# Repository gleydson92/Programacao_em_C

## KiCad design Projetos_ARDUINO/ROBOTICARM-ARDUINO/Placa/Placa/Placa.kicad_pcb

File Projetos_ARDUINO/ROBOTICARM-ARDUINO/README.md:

# RobotArm
Projeto de Braço Robótico para tutoria da Universidade Positivo

links:
http://letsmakerobots.com/node/21633
http://letsmakerobots.com/node/42704
http://letsmakerobots.com/files/field_primary_image/Still_3.jpeg?
https://www.pinterest.com/pin/126804545735484398/?from_navigate=true
http://www.instructables.com/id/DIY-Arduino-Robotic-Arm/step2/Step-2-Assemble-the-base-and-forearms/

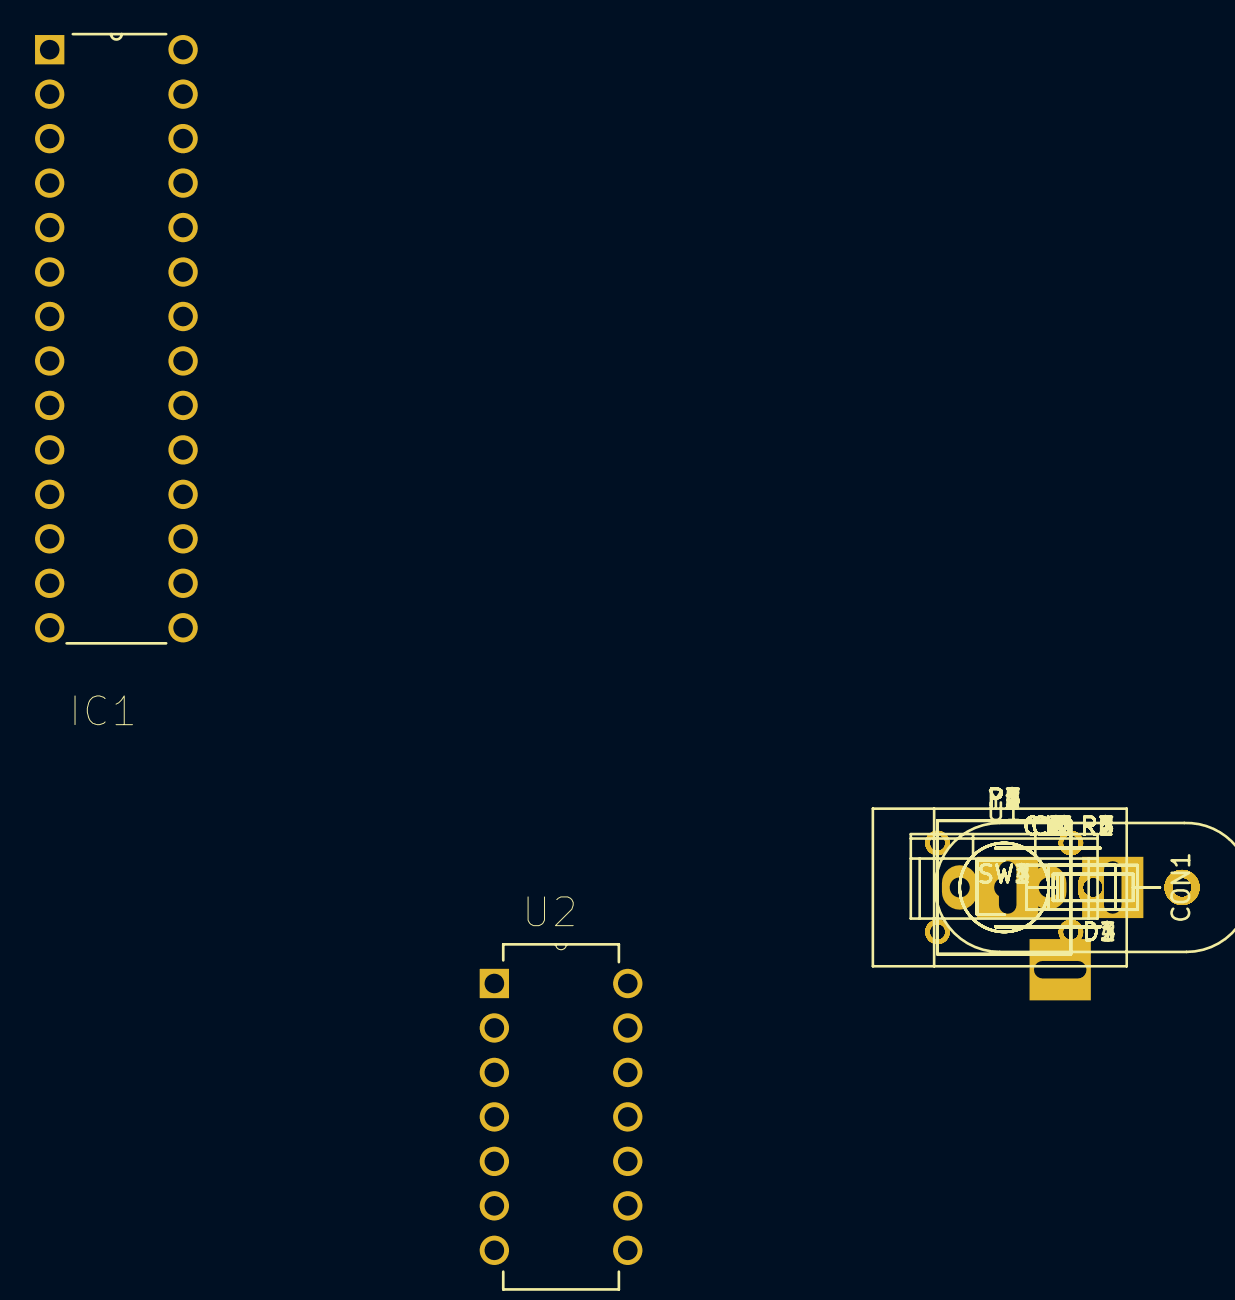
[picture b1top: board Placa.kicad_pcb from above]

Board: 2 copper layers, 43 parts (0 on the bottom side), 24 nets, no tracks yet.

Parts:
C1, C2, C5, C6, C7: C; C_Disc_D6_P5
C3, C4, C8, C9, C10, C11, C12, C13, C14, C15: CP; C_Disc_D6_P5
CON1: BARREL_JACK
D1, D2, D3, D4: D; Diode_DO-35_SOD27_Horizontal_RM10
IC1: ATMEGA328-P; DIP254P762X457-28
P1: POT1; Socket_Strip_Straight_1x03
P2: POT2; Socket_Strip_Straight_1x03
P3: POT3; Socket_Strip_Straight_1x03
P4: SERVO1; Socket_Strip_Straight_1x03
P5: SERVO2; Socket_Strip_Straight_1x03
P6: SERVO3; Socket_Strip_Straight_1x03
P7: SERVO4; Socket_Strip_Straight_1x03
P8: POT4; Socket_Strip_Straight_1x03
R1, R2, R3, R4, R5, R6, R7: R; Resistor_Horizontal_RM10mm
SW1, SW2, SW3, SW4: Switch_DPST; SW_PUSH_SMALL
U1: 78L05; TO-220
U2: 40106; DIP254P762X508-14
Y1: Crystal; HC-33UV

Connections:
GND: C1.2, C2.2, C3.2, C4.2, C5.2, C6.2, C7.2, C8.2, C9.2, C10.2, C11.2, C12.2, C13.2, C14.2, C15.2, CON1.2, CON1.3, IC1.8, IC1.22, P1.3, P2.3, P3.3, P4.3, P5.3, P6.3, P7.3, P8.3, SW1.2, SW2.2, SW3.2, SW4.2
unnamed: C1.1, IC1.9, Y1.1
unnamed: C2.1, IC1.10, Y1.2
unnamed: C3.1, D1.1
unnamed: C5.1, D2.1, R2.2, SW2.1, U2.1
unnamed: C6.1, D3.1, R3.2, SW3.1, U2.3
unnamed: C7.1, D4.1, R4.2, SW4.1, U2.5
unnamed: C4.1, C8.1, C9.1, C10.1, C11.1, C12.1, C13.1, C14.1, C15.1, IC1.7, P1.1, P2.1, P3.1, P4.2, P5.2, P6.2, P7.2, P8.1, R1.2, R5.1, R6.1, R7.2
unnamed: CON1.1, D1.2
unnamed: D2.2, R2.1, R5.2
unnamed: D3.2, R3.1, R6.2
unnamed: D4.2, R4.1, R7.1
unnamed: IC1.1, R1.1, SW1.1
unnamed: IC1.4, U2.2
unnamed: IC1.5, P4.1
unnamed: IC1.15, P5.1
unnamed: IC1.16, P6.1
unnamed: IC1.17, P7.1
unnamed: IC1.18, U2.4
unnamed: IC1.19, U2.6
unnamed: IC1.23, P1.2
unnamed: IC1.24, P2.2
unnamed: IC1.25, P3.2
unnamed: IC1.26, P8.2

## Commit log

2016-07-19 Primeiros Updates
2016-07-25 Atualização Emergencial
2016-08-13 Atualização
2016-08-14 Directory
2016-09-05 Atualização de Scripts
2016-10-20 Atualização(VeiWatch)
2016-10-24 VeiWatch
2016-11-04 Teste Display NOKIA5110
2016-11-04 Testes Display NOKIA 5110
2016-11-04 Teste Display
2016-11-04 Testes com O Display
2016-11-05 Teste VeiWatch
2016-11-05 Testes com o VeiWatch
2016-11-05 Teste com PCD8544
2016-11-05 Teste com o Display 5110
2016-11-06 Teste com o Display NOKIA
2016-11-07 Teste Placa
2016-11-08 Firmware OK
2016-11-08 Teste das Telas
2016-11-09 Testes com as telas: Principal e Sensores
2016-11-10 Teste de Text Scrolling
2016-11-10 Tentativa de scroll Text mal sucedida
2016-11-10 Scroll Teste
2016-11-10 Tela de Perfil
2016-11-13 Testes com o código main.c
2016-11-13 Testes com as telas
2016-11-13 Atualizações no código principal
2016-11-13 Teste com os Layouts
2016-11-14 Teste com o Display
2016-11-14 Testes
2016-11-14 Testes finais
2016-11-17 Teste.c
2016-11-17 Lista
2016-11-18 Testes em andamento
2016-11-29 Trabalho Perreto
